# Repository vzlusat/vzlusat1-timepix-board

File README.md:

# VZLUSAT-1 Timepix board materials

## Publications

```
Baca, T., et al.
"Timepix in LEO Orbit onboard the VZLUSAT-1 Nanosatellite:
1-year of Space Radiation Dosimetry Measurements."
Journal of Instrumentation 13.11 (2018): C11010.
```

```
Baca, T., et al.
"Miniaturized X-ray telescope for VZLUSAT-1 nanosatellite with Timepix detector."
Journal of Instrumentation 11.10 (2016): C10007.
```

```
Urban, Martin, et al.
"VZLUSAT-1: Nanosatellite with miniature lobster eye X-ray telescope
and qualification of the radiation shielding composite for space application."
Acta Astronautica 140 (2017): 96-104.
```

```
Daniel, Vladimír, et al.
"In-Orbit Commissioning of Czech Nanosatellite VZLUSAT-1 for the QB50 Mission
with a Demonstrator of a Miniaturised Lobster-Eye X-Ray Telescope
and Radiation Shielding Composite Materials."
Space Science Reviews 215.5 (2019): 40.
```

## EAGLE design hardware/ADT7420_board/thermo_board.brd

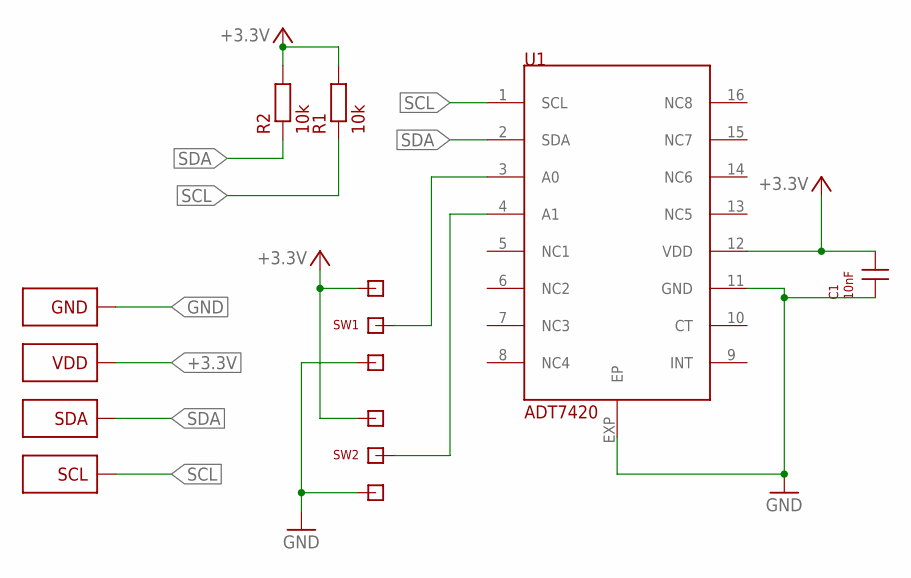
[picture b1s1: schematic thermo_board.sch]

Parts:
C1: 10nF; R0402
GND: CONN_PAD_SQUARE
R1, R2: 10k; R0402
SCL: CONN_PAD_ROUND
SDA: CONN_PAD_ROUND
SW1, SW2: SOLDER_SWITCH_TWO; SOLDER_SWITCH
U1: ADT7420; LFCSP16
VDD: CONN_PAD_ROUND

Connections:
+3.3V: C1.2, R1.2, R2.2, SW1.1 (2), SW2.1 (2), U1.12 (VDD), VDD.P$1
GND: C1.1, GND.P$1, SW1.2 (1), SW2.2 (1), U1.11 (GND), U1.EXP (EP)
unnamed: SW1.MID, U1.3 (A0)
unnamed: SW2.MID, U1.4 (A1)
SCL: R1.1, SCL.P$1, U1.1 (SCL)
SDA: R2.1, SDA.P$1, U1.2 (SDA)

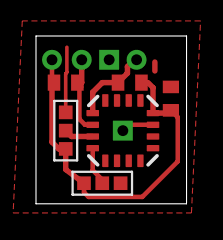
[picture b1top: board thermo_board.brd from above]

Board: 2 copper layers, 8.4 x 9.3 mm, 10 parts (0 on the bottom side), 6 nets.

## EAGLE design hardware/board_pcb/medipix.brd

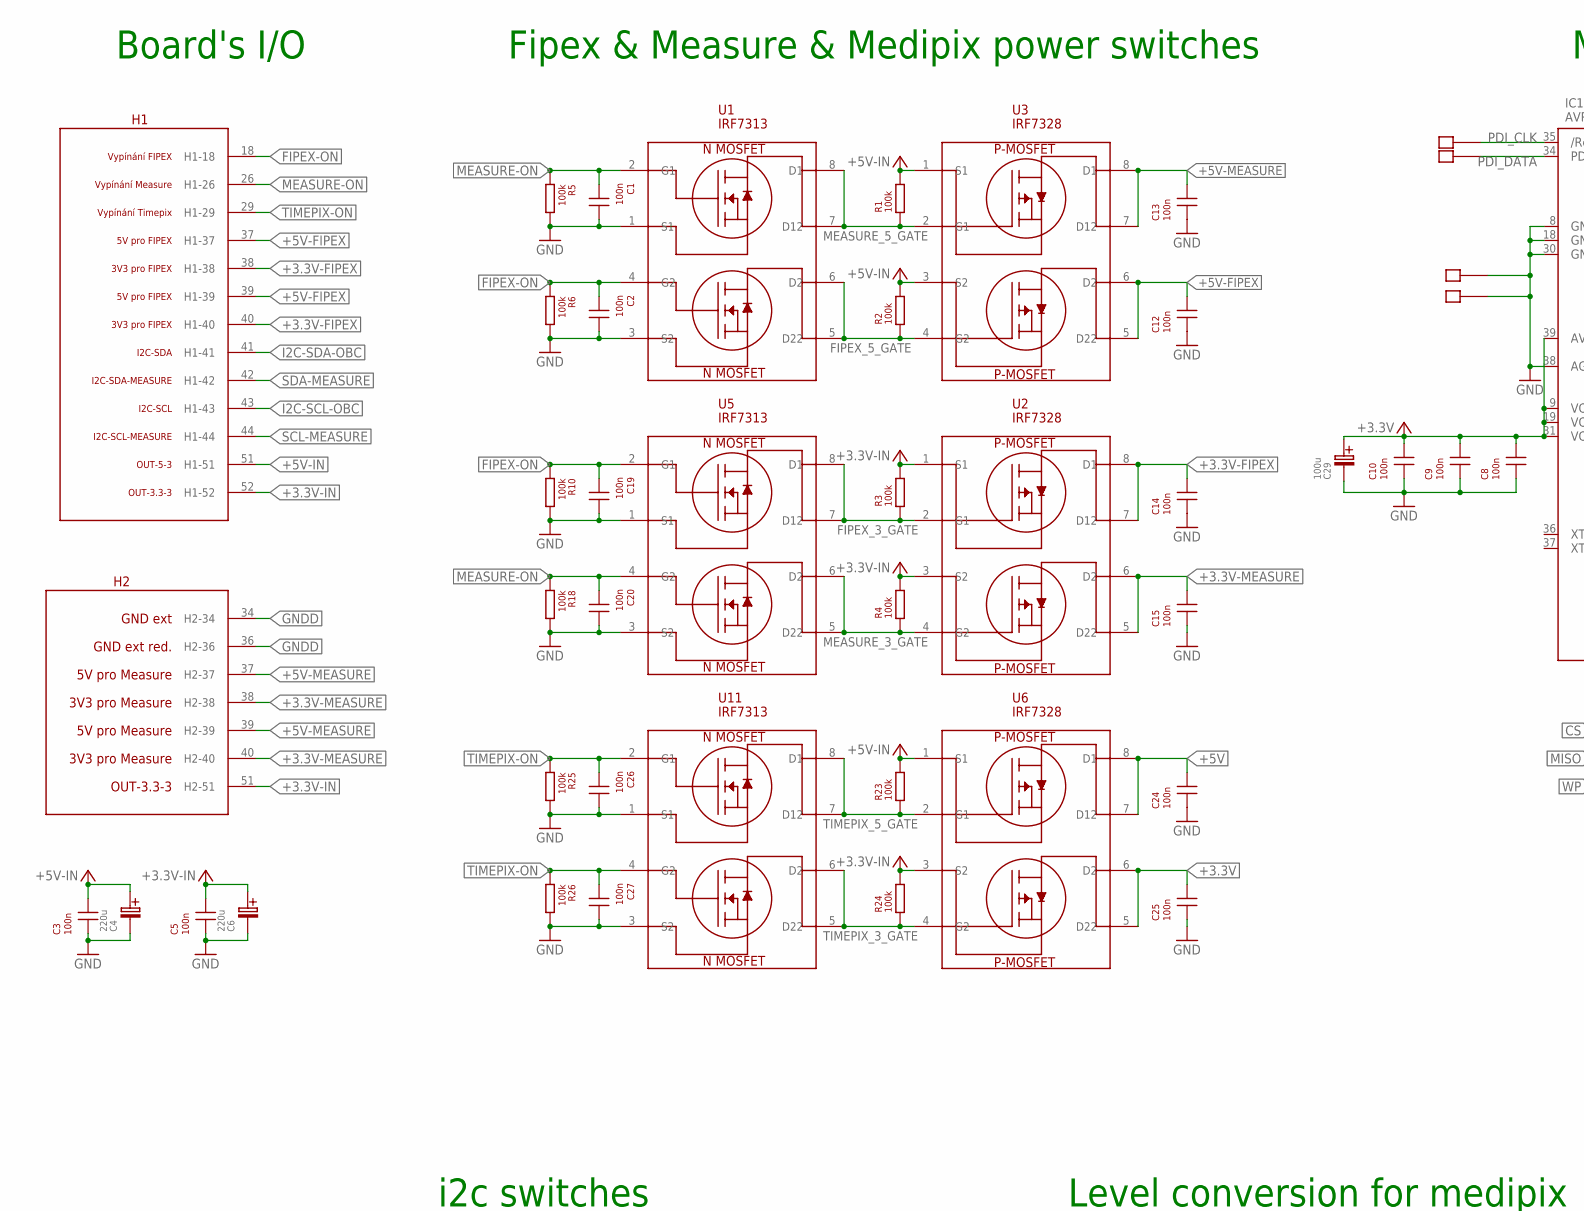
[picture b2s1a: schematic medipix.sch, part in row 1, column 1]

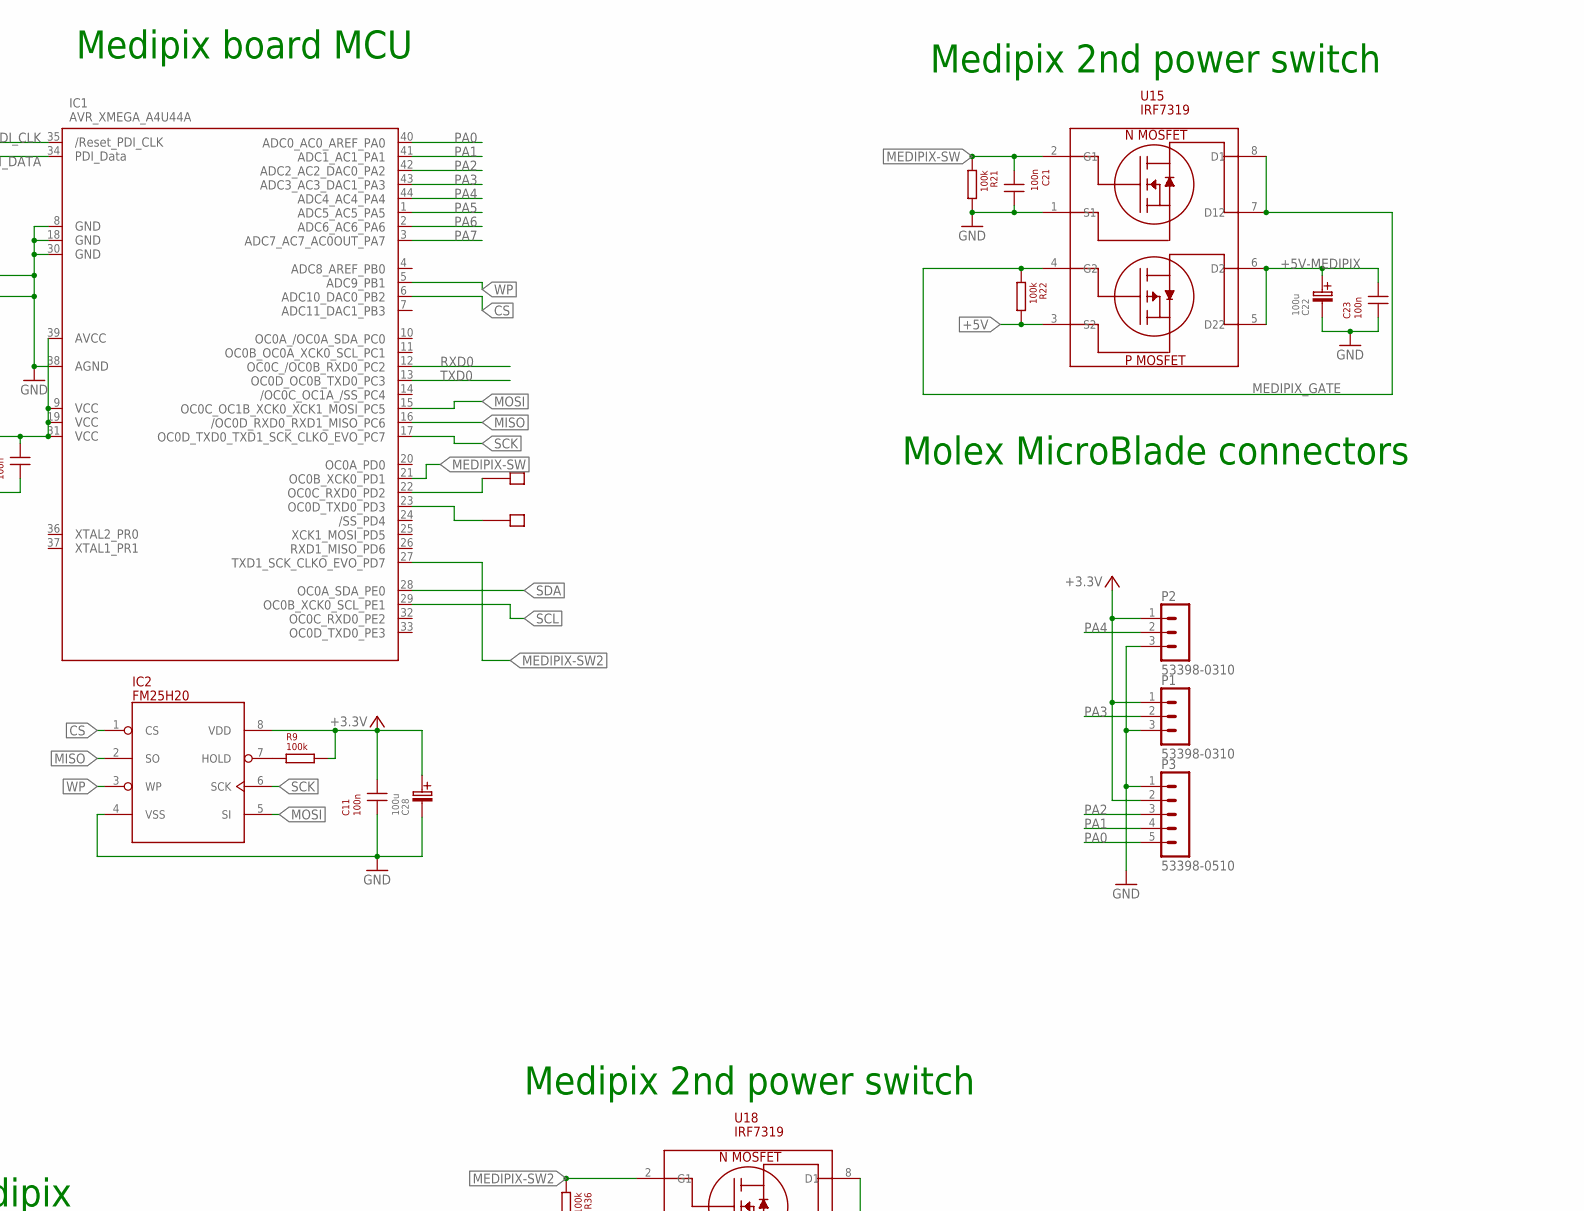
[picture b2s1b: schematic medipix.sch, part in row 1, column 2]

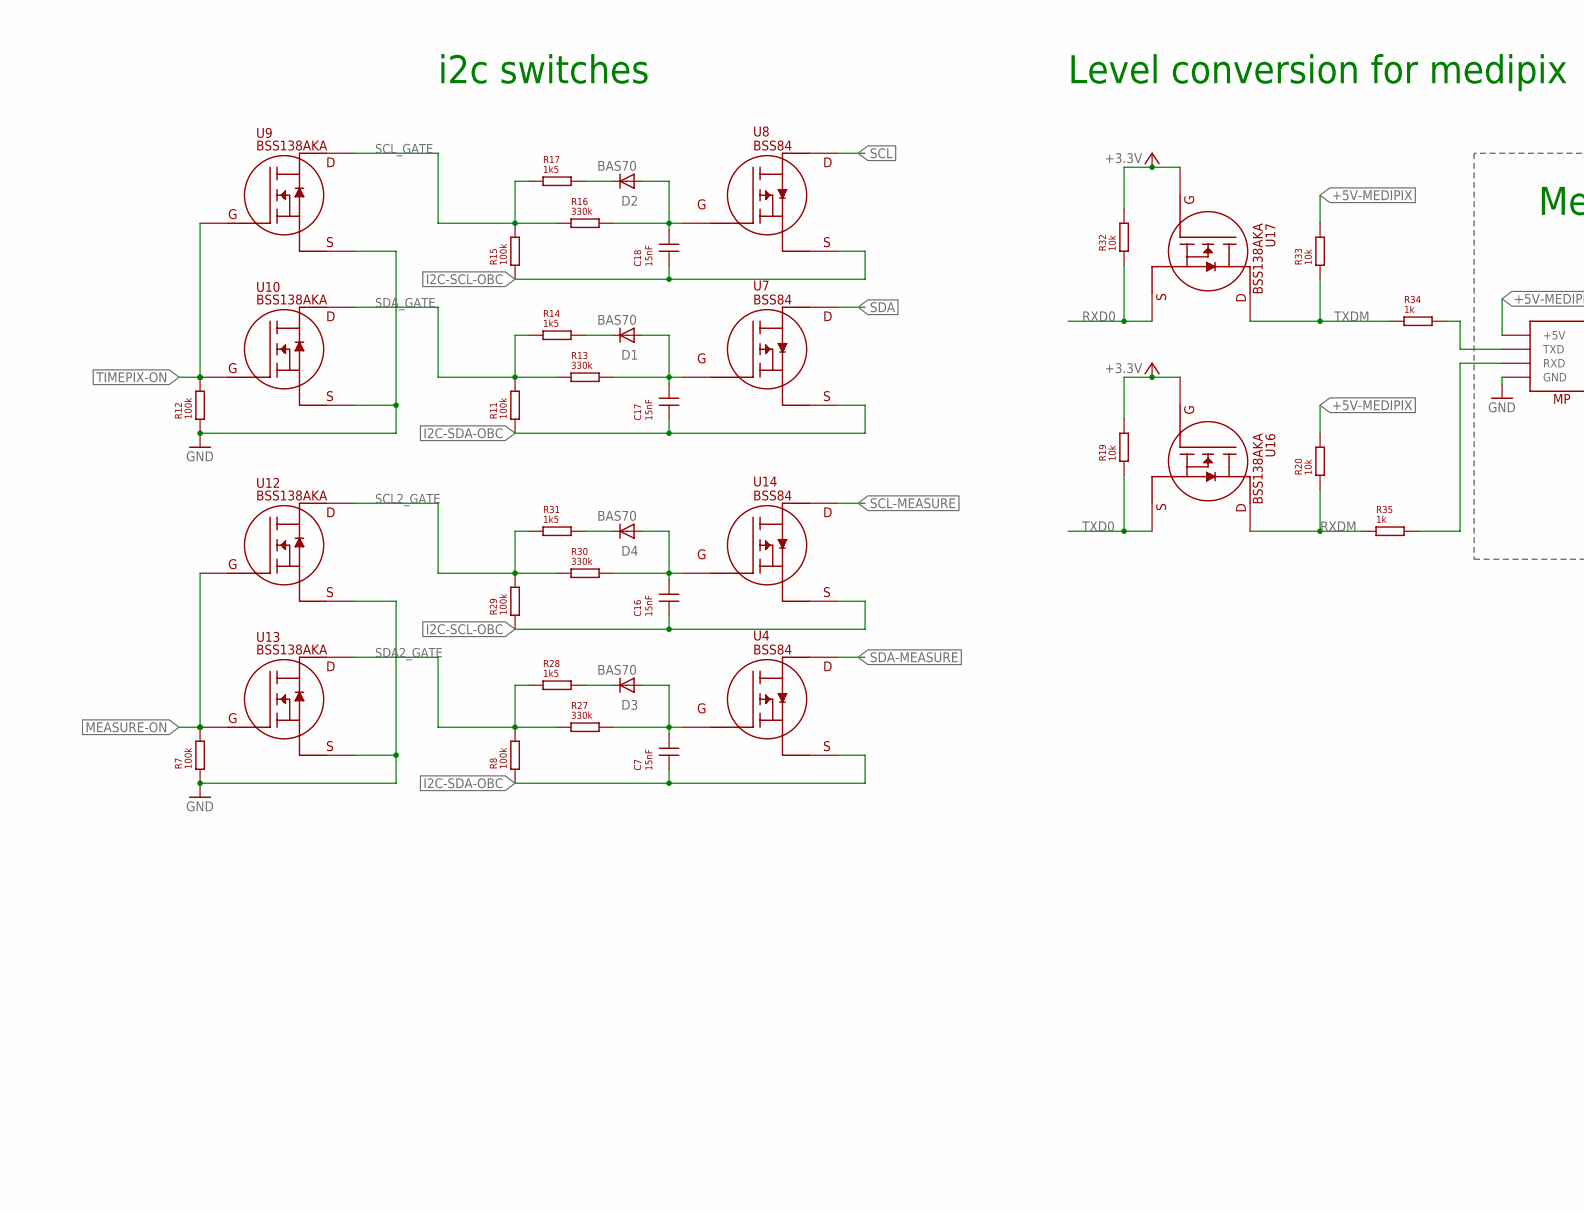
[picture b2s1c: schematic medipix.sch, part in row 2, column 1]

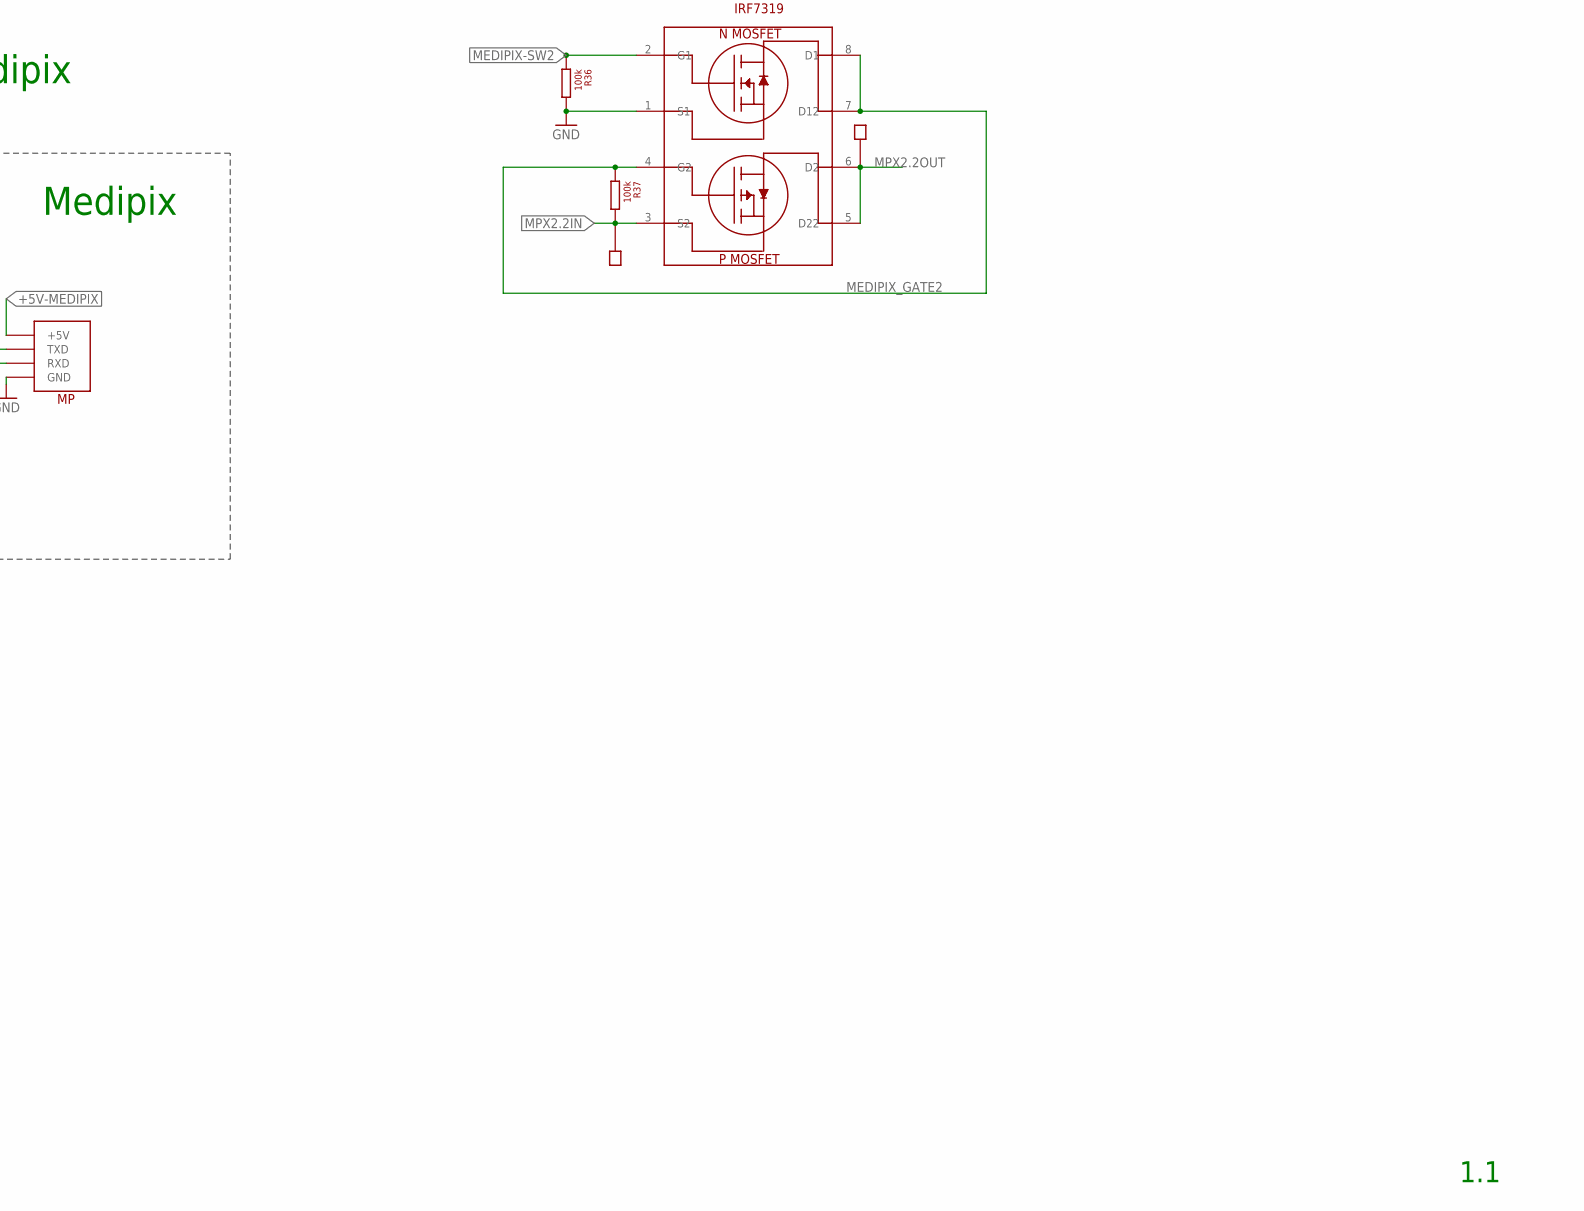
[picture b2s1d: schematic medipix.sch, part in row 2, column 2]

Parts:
C1, C2, C3, C5, C8, C9, C10, C11, C12, C13, C14, C15, C19, C20, C21, C23, C24, C25, C26, C27: 100n; R0805
C4, C6: 220u; D
C7, C16, C17, C18: 15nF; R0805
C22, C28, C29: 100u; SMC_B
CLK: CLK; PIN
D1, D2, D3, D4: BAS70; SOD523
DATA: DATA; PIN
GND, GND1: GND; PIN
H1: H1; H-KONEKTOR
H2: H2; H-KONEKTOR
IC1: AVR_XMEGA_A4U44A; TQFP44
IC2: FM25H20; SOIC08
MP: MEDIPIX_CONNECTOR
P1, P2: 53398-0310
P3: 53398-0510
R1, R2, R3, R4, R5, R6, R7, R8, R9, R10, R11, R12, R15, R18, R21, R22, R23, R24, R25, R26, R29, R36, R37: 100k; R0805
R13, R16, R27, R30: 330k; R0805
R14, R17, R28, R31: 1k5; R0805
R19, R20, R32, R33: 10k; R0805
R34, R35: 1k; R0805
RXD0: RX; PIN
TXD0: TX; PIN
TXD1: IN; PIN
TXD2: OUT; PIN
U1, U5, U11: IRF7313; SOIC08
U2, U3, U6: IRF7328; SOIC08
U4, U7, U8, U14: BSS84; SOT-23
U9, U10, U12, U13, U16, U17: BSS138AKA; SOT-23
U15, U18: IRF7319; SOIC08

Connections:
+3.3V: C8.2, C9.2, C10.2, C11.2, C25.2, C28.+ (C_EL+), C29.+ (C_EL+), IC1.9 (VCC1), IC1.19 (VCC2), IC1.31 (VCC3), IC1.39 (AVCC), IC2.8 (VDD), P1.1, P2.1, P3.2, R9.2, R19.2, R32.2, U6.5 (D22), U6.6 (D2), U16.1 (G), U17.1 (G); also elsewhere on the board
+3.3V-FIPEX: C14.2, H1.38 (H1-38), H1.40 (H1-40), U2.7 (D12), U2.8 (D1)
+3.3V-IN: C5.2, C6.+ (C_EL+), H1.52 (H1-52), H2.51 (H2-51), R3.2, R4.2, R24.2, U2.1 (S1), U2.3 (S2), U6.3 (S2); also elsewhere on the board
+3.3V-MEASURE: C15.2, H2.38 (H2-38), H2.40 (H2-40), U2.5 (D22), U2.6 (D2)
+5V: C24.2, R22.2, U6.7 (D12), U6.8 (D1), U15.3 (S2)
+5V-FIPEX: C12.2, H1.37 (H1-37), H1.39 (H1-39), U3.5 (D22), U3.6 (D2)
+5V-IN: C3.2, C4.+ (C_EL+), H1.51 (H1-51), R1.2, R2.2, R23.2, U3.1 (S1), U3.3 (S2), U6.1 (S1); also elsewhere on the board
+5V-MEASURE: C13.2, H2.37 (H2-37), H2.39 (H2-39), U3.7 (D12), U3.8 (D1)
+5V-MEDIPIX: C22.+ (C_EL+), C23.2, MP.5V (+5V), R20.2, R33.2, U15.5 (D22), U15.6 (D2)
CS: IC1.6 (PB2), IC2.1 (CS)
FIPEX-ON: C2.1, C19.1, H1.18 (H1-18), R6.1, R10.1, U1.4 (G2), U5.2 (G1)
FIPEX_3_GATE: R3.1, U2.2 (G1), U5.7 (D12), U5.8 (D1)
FIPEX_5_GATE: R2.1, U1.5 (D22), U1.6 (D2), U3.4 (G2)
GNDD: C1.2, C2.2, C3.1, C4.- (C_EL-), C5.1, C6.- (C_EL-), C8.1, C9.1, C10.1, C11.1, C12.1, C13.1, C14.1, C15.1, C19.2, C20.2, C21.2, C22.- (C_EL-), C23.1, C24.1, C25.1, C26.2, C27.2, C28.- (C_EL-), C29.- (C_EL-), GND.P$1, GND1.P$1, H2.34 (H2-34), H2.36 (H2-36), IC1.8 (GND1), IC1.18 (GND2), IC1.30 (GND3), IC1.38 (AGND), IC2.4 (VSS), MP.GND, P1.3, P2.3, P3.1, R5.2, R6.2, R7.1, R10.2, R12.1, R18.2, R21.2, R25.2, R26.2, R36.2, U1.1 (S1), U1.3 (S2), U5.1 (S1), U5.3 (S2), U9.2 (S), U10.2 (S), U11.1 (S1), U11.3 (S2), U12.2 (S), U13.2 (S), U15.1 (S1), U18.1 (S1)
I2C-SCL-OBC: C16.1, C18.1, H1.43 (H1-43), R15.1, R29.1, U8.2 (S), U14.2 (S)
I2C-SDA-OBC: C7.1, C17.1, H1.41 (H1-41), R8.1, R11.1, U4.2 (S), U7.2 (S)
MEASURE-ON: C1.1, C20.1, H1.26 (H1-26), R5.1, R7.2, R18.1, U1.2 (G1), U5.4 (G2), U12.1 (G), U13.1 (G)
MEASURE_3_GATE: R4.1, U2.4 (G2), U5.5 (D22), U5.6 (D2)
MEASURE_5_GATE: R1.1, U1.7 (D12), U1.8 (D1), U3.2 (G1)
MEDIPIX-SW: C21.1, IC1.21 (PD1), R21.1, U15.2 (G1)
MEDIPIX-SW2: IC1.27 (PD7), R36.1, U18.2 (G1)
MEDIPIX_GATE: R22.1, U15.4 (G2), U15.7 (D12), U15.8 (D1)
MEDIPIX_GATE2: R37.1, U18.4 (G2), U18.7 (D12), U18.8 (D1)
MISO: IC1.16 (PC6), IC2.2 (SO)
MOSI: IC1.15 (PC5), IC2.5 (SI)
MPX2.2IN: R37.2, TXD1.P$1, U18.3 (S2)
MPX2.2OUT: TXD2.P$1, U18.5 (D22), U18.6 (D2)
unnamed: D3.C, R28.2
unnamed: C7.2, D3.A, R27.2, U4.1 (G)
unnamed: D2.C, R17.2
unnamed: D1.C, R14.2
unnamed: C17.2, D1.A, R13.2, U7.1 (G)
unnamed: C18.2, D2.A, R16.2, U8.1 (G)
unnamed: IC2.7 (HOLD), R9.1
unnamed: MP.P$4 (TXD), R34.2
unnamed 37: IC1.11 (PC1); also elsewhere on the board
unnamed 38: IC1.10 (PC0); also elsewhere on the board
unnamed: D4.C, R31.2
unnamed: C16.2, D4.A, R30.2, U14.1 (G)
unnamed: IC1.22 (PD2), RXD0.P$1
unnamed: IC1.23 (PD3), TXD0.P$1
PA0: IC1.40 (PA0), P3.5
PA1: IC1.41 (PA1), P3.4
PA2: IC1.42 (PA2), P3.3
PA3: IC1.43 (PA3), P1.2
PA4: IC1.44 (PA4), P2.2
PA5: IC1.1 (PA5)
PA6: IC1.2 (PA6)
PA7: IC1.3 (PA7)
PDI_CLK: CLK.P$1, IC1.35 (RESET)
PDI_DATA: DATA.P$1, IC1.34 (PDI_DATA)
RXD0: IC1.12 (PC2), R32.1, U17.2 (S)
RXDM: R20.1, R35.1, U16.3 (D)
RXDMMM: MP.P$3 (RXD), R35.2
SCK: IC1.17 (PC7), IC2.6 (SCK)
SCL: IC1.29 (PE1), U8.3 (D)
SCL2_GATE: R29.2, R30.1, R31.1, U12.3 (D)
SCL-MEASURE: H1.44 (H1-44), U14.3 (D)
SCL_GATE: R15.2, R16.1, R17.1, U9.3 (D)
SDA: IC1.28 (PE0), U7.3 (D)
SDA2_GATE: R8.2, R27.1, R28.1, U13.3 (D)
SDA-MEASURE: H1.42 (H1-42), U4.3 (D)
SDA_GATE: R11.2, R13.1, R14.1, U10.3 (D)
TIMEPIX-ON: C26.1, C27.1, H1.29 (H1-29), R12.2, R25.1, R26.1, U9.1 (G), U10.1 (G), U11.2 (G1), U11.4 (G2)
TIMEPIX_3_GATE: R24.1, U6.4 (G2), U11.5 (D22), U11.6 (D2)
TIMEPIX_5_GATE: R23.1, U6.2 (G1), U11.7 (D12), U11.8 (D1)
TXD0: IC1.13 (PC3), R19.1, U16.2 (S)
TXDM: R33.1, R34.1, U17.3 (D)
WP: IC1.5 (PB1), IC2.3 (WP)

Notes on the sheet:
Board's I/O
Fipex & Measure & Medipix power switches
Medipix board MCU
i2c switches
Molex MicroBlade connectors
Medipix 2nd power switch
1.1
Level conversion for medipix
Medipix

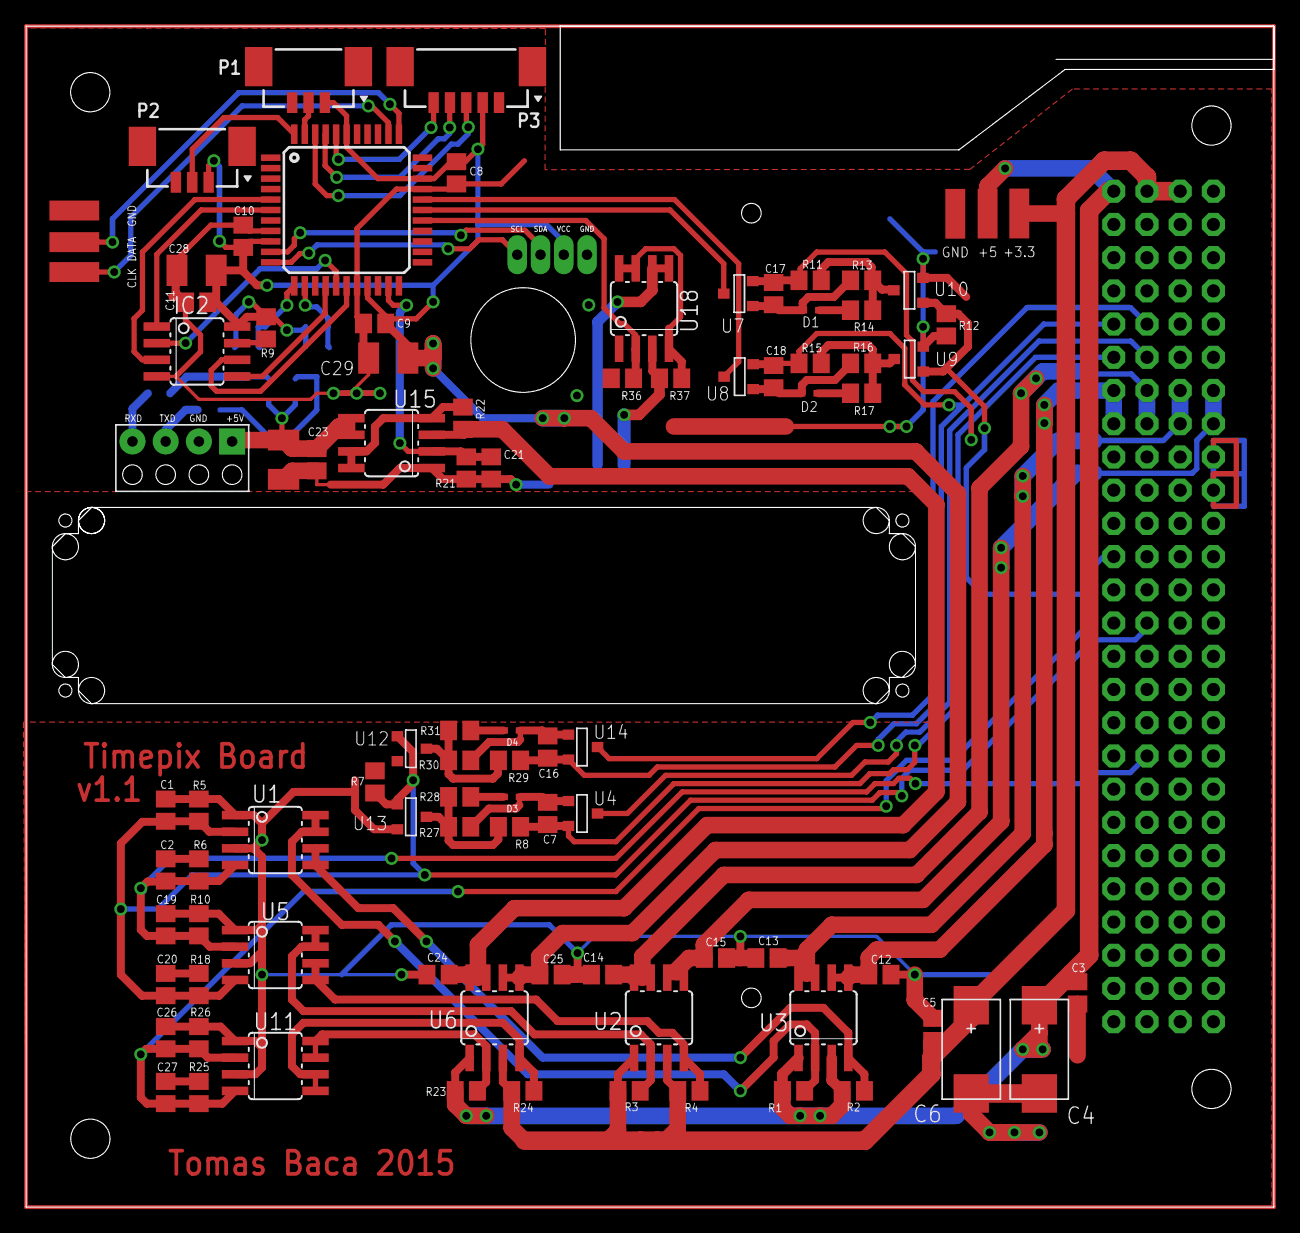
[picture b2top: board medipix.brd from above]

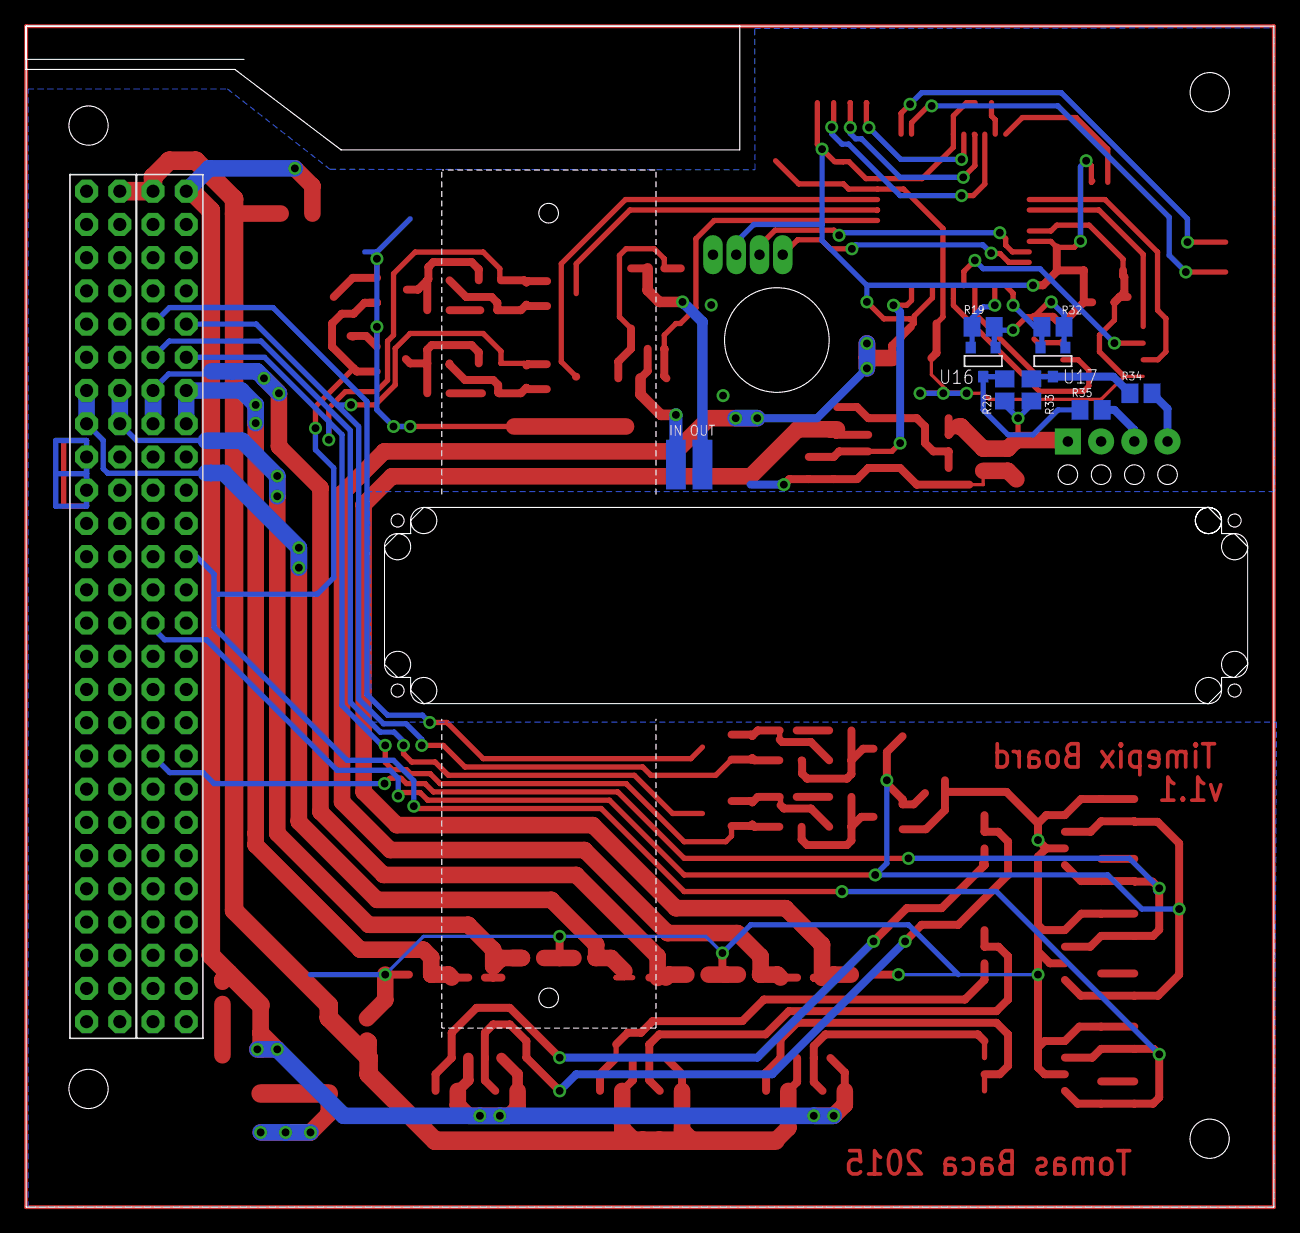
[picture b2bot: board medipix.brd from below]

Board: 2 copper layers, 95.4 x 90.3 mm, 105 parts (12 on the bottom side), 64 nets.

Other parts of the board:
GND25: +3.3; PIN
GND28: +5; PIN
U$1: THERM

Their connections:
+3.3V: U$1.VCC; also elsewhere on the board
+3.3V-IN: GND25.P$1; also elsewhere on the board
+5V-IN: GND28.P$1; also elsewhere on the board
unnamed 37: U$1.SCL; also elsewhere on the board
unnamed 38: U$1.SDA; also elsewhere on the board

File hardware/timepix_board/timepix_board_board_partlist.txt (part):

Partlist

Exported from medipix.sch at 19.3.2015 9:49:41

EAGLE Version 6.5.0 Copyright (c) 1988-2013 CadSoft

Assembly variant: 

Part     Value             Device             Package           Library             Sheet

C1       100n              CAPACITOR_CERAMIC  R0805             medipix             1
C2       100n              CAPACITOR_CERAMIC  R0805             medipix             1
C3       100n              CAPACITOR_CERAMIC  R0805             medipix             1
C4       220u              CAPACITOR_TANTAL_D D                 medipix             1
C5       100n              CAPACITOR_CERAMIC  R0805             medipix             1
C6       220u              CAPACITOR_TANTAL_D D                 medipix             1
C7       15nF              CAPACITOR_CERAMIC  R0805             medipix             1
C8       100n              CAPACITOR_CERAMIC  R0805             medipix             1
C9       100n              CAPACITOR_CERAMIC  R0805             medipix             1
C10      100n              CAPACITOR_CERAMIC  R0805             medipix             1
C11      100n              CAPACITOR_CERAMIC  R0805             medipix             1
C12      100n              CAPACITOR_CERAMIC  R0805             medipix             1
C13      100n              CAPACITOR_CERAMIC  R0805             medipix             1
C14      100n              CAPACITOR_CERAMIC  R0805             medipix             1
C15      100n              CAPACITOR_CERAMIC  R0805             medipix             1
C16      15nF              CAPACITOR_CERAMIC  R0805             medipix             1
C17      15nF              CAPACITOR_CERAMIC  R0805             medipix             1
C18      15nF              CAPACITOR_CERAMIC  R0805             medipix             1
C19      100n              CAPACITOR_CERAMIC  R0805             medipix             1
C20      100n              CAPACITOR_CERAMIC  R0805             medipix             1
C21      100n              CAPACITOR_CERAMIC  R0805             medipix             1
C22      100u              CAPACITOR_TANTAL_B SMC_B             medipix             1
C23      100n              CAPACITOR_CERAMIC  R0805             medipix             1
C24      100n              CAPACITOR_CERAMIC  R0805             medipix             1
C25      100n              CAPACITOR_CERAMIC  R0805             medipix             1
C26      100n              CAPACITOR_CERAMIC  R0805             medipix             1
C27      100n              CAPACITOR_CERAMIC  R0805             medipix             1
C28      100u              CAPACITOR_TANTAL_B SMC_B             medipix             1
C29      100u              CAPACITOR_TANTAL_B SMC_B             medipix             1
CLK      CLK               PIN                PIN               medipix             1
D1       BAS70             BAS70              SOD523            medipix             1
D2       BAS70             BAS70              SOD523            medipix             1
D3       BAS70             BAS70              SOD523            medipix             1
D4       BAS70             BAS70              SOD523            medipix             1
DATA     DATA              PIN                PIN               medipix             1
GND      GND               PIN                PIN               medipix             1
GND1     GND               PIN                PIN               medipix             1
GND25    +3.3              PIN                PIN               medipix             1
GND28    +5                PIN                PIN               medipix             1
H1       H1                H1                 H-KONEKTOR        medipix             1
H2       H2                H2                 H-KONEKTOR        medipix             1
IC1      AVR_XMEGA_A4U44A  AVR_XMEGA_A4U44A   TQFP44            medipix             1
IC2      FM25H20           FM25H20            SOIC08            medipix             1
MP       MEDIPIX_CONNECTOR MEDIPIX_CONNECTOR  MEDIPIX_CONNECTOR medipix             1
P1       PICOBLADE         53398-0310         53398-0310        con-molex-picoblade 1
P2       PICOBLADE         53398-0310         53398-0310        con-molex-picoblade 1
P3       PICOBLADE         53398-0510         53398-0510        con-molex-picoblade 1
R1       100k              RESISTOR0805       R0805             medipix             1
R2       100k              RESISTOR0805       R0805             medipix             1
R3       100k              RESISTOR0805       R0805             medipix             1
R4       100k              RESISTOR0805       R0805             medipix             1
R5       100k              RESISTOR0805       R0805             medipix             1
R6       100k              RESISTOR0805       R0805             medipix             1
R7       100k              RESISTOR0805       R0805             medipix             1
R8       100k              RESISTOR0805       R0805             medipix             1
R9       100k              RESISTOR0805       R0805             medipix             1
R10      100k              RESISTOR0805       R0805             medipix             1
R11      100k              RESISTOR0805       R0805             medipix             1
R12      100k              RESISTOR0805       R0805             medipix             1
R13      330k              RESISTOR0805       R0805             medipix             1
R14      1k5               RESISTOR0805       R0805             medipix             1
R15      100k              RESISTOR0805       R0805             medipix             1
R16      330k              RESISTOR0805       R0805             medipix             1
R17      1k5               RESISTOR0805       R0805             medipix             1
R18      100k              RESISTOR0805       R0805             medipix             1
R19      10k               RESISTOR0805       R0805             medipix             1
R20      10k               RESISTOR0805       R0805             medipix             1
R21      100k              RESISTOR0805       R0805             medipix             1
R22      100k              RESISTOR0805       R0805             medipix             1
R23      100k              RESISTOR0805       R0805             medipix             1
R24      100k              RESISTOR0805       R0805             medipix             1
R25      100k              RESISTOR0805       R0805             medipix             1
R26      100k              RESISTOR0805       R0805             medipix             1
R27      330k              RESISTOR0805       R0805             medipix             1
R28      1k5               RESISTOR0805       R0805             medipix             1
R29      100k              RESISTOR0805       R0805             medipix             1
R30      330k              RESISTOR0805       R0805             medipix             1
R31      1k5               RESISTOR0805       R0805             medipix             1
R32      10k               RESISTOR0805       R0805             medipix             1
R33      10k               RESISTOR0805       R0805             medipix             1
R34      1k                RESISTOR0805       R0805             medipix             1
R35      1k                RESISTOR0805       R0805             medipix             1
R36      100k              RESISTOR0805       R0805             medipix             1
R37      100k              RESISTOR0805       R0805             medipix             1
TXD1     IN                PIN                PIN               medipix             1
TXD2     OUT               PIN                PIN               medipix             1
U$1      THERM             THERM              THERM             medipix             1
U1       IRF7313           IRF7313            SOIC08            medipix             1
U2       IRF7328           IRF7328            SOIC08            medipix             1
U3       IRF7328           IRF7328            SOIC08            medipix             1
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
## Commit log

2014-08-31 :octocat: Added .gitattributes & .gitignore files
2014-08-31 Initial commit
    Added copy of FreeRTOS-on-ATxmega128a4u repository
2014-08-31 Proper clock setup
2014-09-06 gitignore update
2014-10-03 + LibCSP
2014-10-11 LibCSP almost working
2014-10-12 Cubesat Space Protocol working
2014-10-12 Merged from deveop
2014-10-12 MPX = 0
2014-11-02 CSP working with OBC
    + BAUDrate fix
    + HouseKeeping routine
    + some other fixes
2014-11-02 Branch created
2014-11-02 + Medipix communication
2014-11-12 + Medipix switch
2014-11-13 Medipix toggeling routine
2014-11-25 Medipix receiving corrected
2014-11-27 Version for 1st tests
2015-01-25 After 1st tests
2015-02-04 + Medipix readout
2015-02-11 + new connectors, + medipix 2.2V switch
2015-02-15 Medipix readout working properly
2015-02-22 + Board updated with temperature sensor connector
2015-03-01 Deska pro teplomer
2015-03-03 Thermo board sent out
2015-04-15 Thermo board dalsi podklady
2015-05-30 + Timepix hw layer
2015-05-30 + EqualizationParser
2015-05-30 + RNCGenerator
2015-06-05 + readout bug fixed
2015-06-05 + huhl
2015-06-07 It should work
2015-06-07 Uz se blizime
2015-06-08 HuhlyHuhly
2015-06-08 Dnes snad konec
2015-06-08 Tak uz
2015-06-08 + matlab + kit
2015-06-08 Mereni
2015-06-08 + mask and printing script
2015-06-10 Mereni presun
2015-06-10 + fram and adt
2015-06-10 mode change fixed
2015-06-10 update s Fram, zatim nejde
2015-06-10 + nove mereni
2015-06-11 FRAM jede
2015-06-11 + urceni orientace cipu
2015-06-12 + legendy k mereni
2015-06-25 Towards the filtering
2015-06-25 Filtering works
2015-06-26 Filtrace + statistika ok
2015-06-28 + compressed readout
2015-06-29 Binning is working
2015-06-30 Delays during startup shortened, exposition time fixed
2015-06-30 bootup and measuring faster
2015-07-02 Equalization Fixed, Bias fixe, Thr fixe, all fixed
2015-07-02 Many fixes, Bias and Thr loading during startup
2015-07-03 + propper equalization of the flight medipix
2015-07-03 + equalizace eqm
2015-07-03 Equalization depending on the mounted medipix
2015-07-03 Flight model is working OK
2015-07-03 Bleh
2015-07-04 Matlab reworked, Last two line of the detector fixed
2015-07-05 Some bug solved
2015-07-06 ADT should work
2015-07-06 ADT negative values fixed
2015-07-06 Towards OBC commands
2015-07-06 First OBC commands
2015-07-07 + basic DK handling, creating storages, saving HK to DK
2015-07-07 HK and medipix message correctly saving to DK with ACK
2015-07-07 Saving Binned images and histograms to DC
2015-07-07 Saving the raw image to DK :-)
2015-07-07 Blah, stále funguje matlab přístup
2015-07-07 + image saver and plotter
2015-07-08 blah
2015-07-08 Time from OBC ok
2015-07-08 Towards reading the attitude
2015-07-08 Towards attitude from OBC
2015-07-09 + mereni v komore
2015-07-09 Lbah
2015-07-09 Drobne upravy
2015-07-10 + scanning mode
2015-07-12 Small changes
2015-07-13 Mereni presunuto
2015-07-15 1. odevzdany software + měření
    + Verze která byla odevzdaná s letovým kusem, ukládá do DK, měří atp.
    + Měření letového kusu s letovou optikou v komoře
2015-07-16 + UV and IR sensors
2015-07-16 sensor re-typed to signed int
2015-08-16 + multitype output and + energy histogram
2015-08-17 New matlab fix
2015-08-17 + energy histogram to data keeper
2015-08-17 + adrenalin
2015-08-18 Matlab code adjusted to new changes
2015-08-18 Basic structure of decode application
2015-08-19 + packet decoder working in images
2015-08-19 Matlab code adjusted for new version
2015-08-20 HK problem solved
2015-08-21 All commands tested
2015-08-21 upravy na matlab klientovy
2015-08-23 + delays for Matlab
2015-08-23 + readHK in matlab
2015-08-23 Just nothing
2015-08-23 Tightfig removed
2015-08-25 Nahráno do satelitu
2015-09-03 Upgrade FW in the flight board
2015-09-21 Bug fixes
    - getAttitude fixed
    - ack fixed
2015-09-28 + mereni 21.9.2015
    New optics tested in vacuum chamber with X-Ray source.
2015-10-12 + Legenda k mereni 21.9.2015
2015-10-12 Pořádek v měření
2015-10-13 Doplnění readme
2015-10-13 Úprava v readme
2016-01-19 Drobné změny
    Netýkají se softwaru v XMEZE
2016-01-21 Metadata output even with "x so 0"
2016-01-22 Bug fix with sensors minmax
    Flashed to VZLUSAT-1 at 21.1.2016
2016-01-27 + delay between DK packets
2016-02-15 Bug fix
    + fixed bug with uninitialized pointer in ComTask
    + prolonged timeout for getTime
    + added 5ms timeout to waitForDkAck
2016-02-17 Project converted to AS 7.0
    This version was flashed on 16.2.2016
2017-01-17 Fixed bug in creating histograms
2017-01-18 Updated headers for DataKeeper
2017-01-18 Updated firmware in satellite, flashed on 18.1.2017
2017-01-18 Updated image processing and last bugfix in satellite, 18.1.2017
2017-01-19 update DataDecode
2017-03-27 + first prototype of pyDecode
2017-03-27 binn8 parsing should work
2017-03-27 should parse are image types
2017-03-28 first version of gui
2017-03-28 fixed file naming convention
2017-03-28 + metadata showed by pydecode + fixed wrong image parsing
2017-03-28 removed pyc files
2017-03-28 updated gitignore
2017-03-28 pydecode looks good
2017-03-29 partially working calibration
2017-03-30 fixed histogram plotting in pydecode
2017-03-30 fixed gitignore
2017-03-30 data are exported to human and matlab readible form
2017-03-31 updated to v1
2017-03-31 fixed few bugs in v1
2017-03-31 fixed typos and opening of an empty file
2017-04-02 updated exporting to use python csv
2017-04-02 made the main window wider
2017-04-02 fixed python 2 and 3 compatibility issues
2017-04-02 minor changes
2017-04-02 autoinstalling libraries
2017-04-02 updated for windows python 3
2017-04-02 removed redundant script
2017-04-04 added parser for housekeeping
2017-04-04 added housekeeping parsing and visualization
2017-04-10 added readme
2017-06-17 remove xray-decoder, since it has itw own repo
2019-07-08 added assembly firmware for USB Lite
2021-01-03 polishing repo structure

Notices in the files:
parts and their libraries:
con-molex-picoblade: Copyright (C) 2010, Bob Starr
